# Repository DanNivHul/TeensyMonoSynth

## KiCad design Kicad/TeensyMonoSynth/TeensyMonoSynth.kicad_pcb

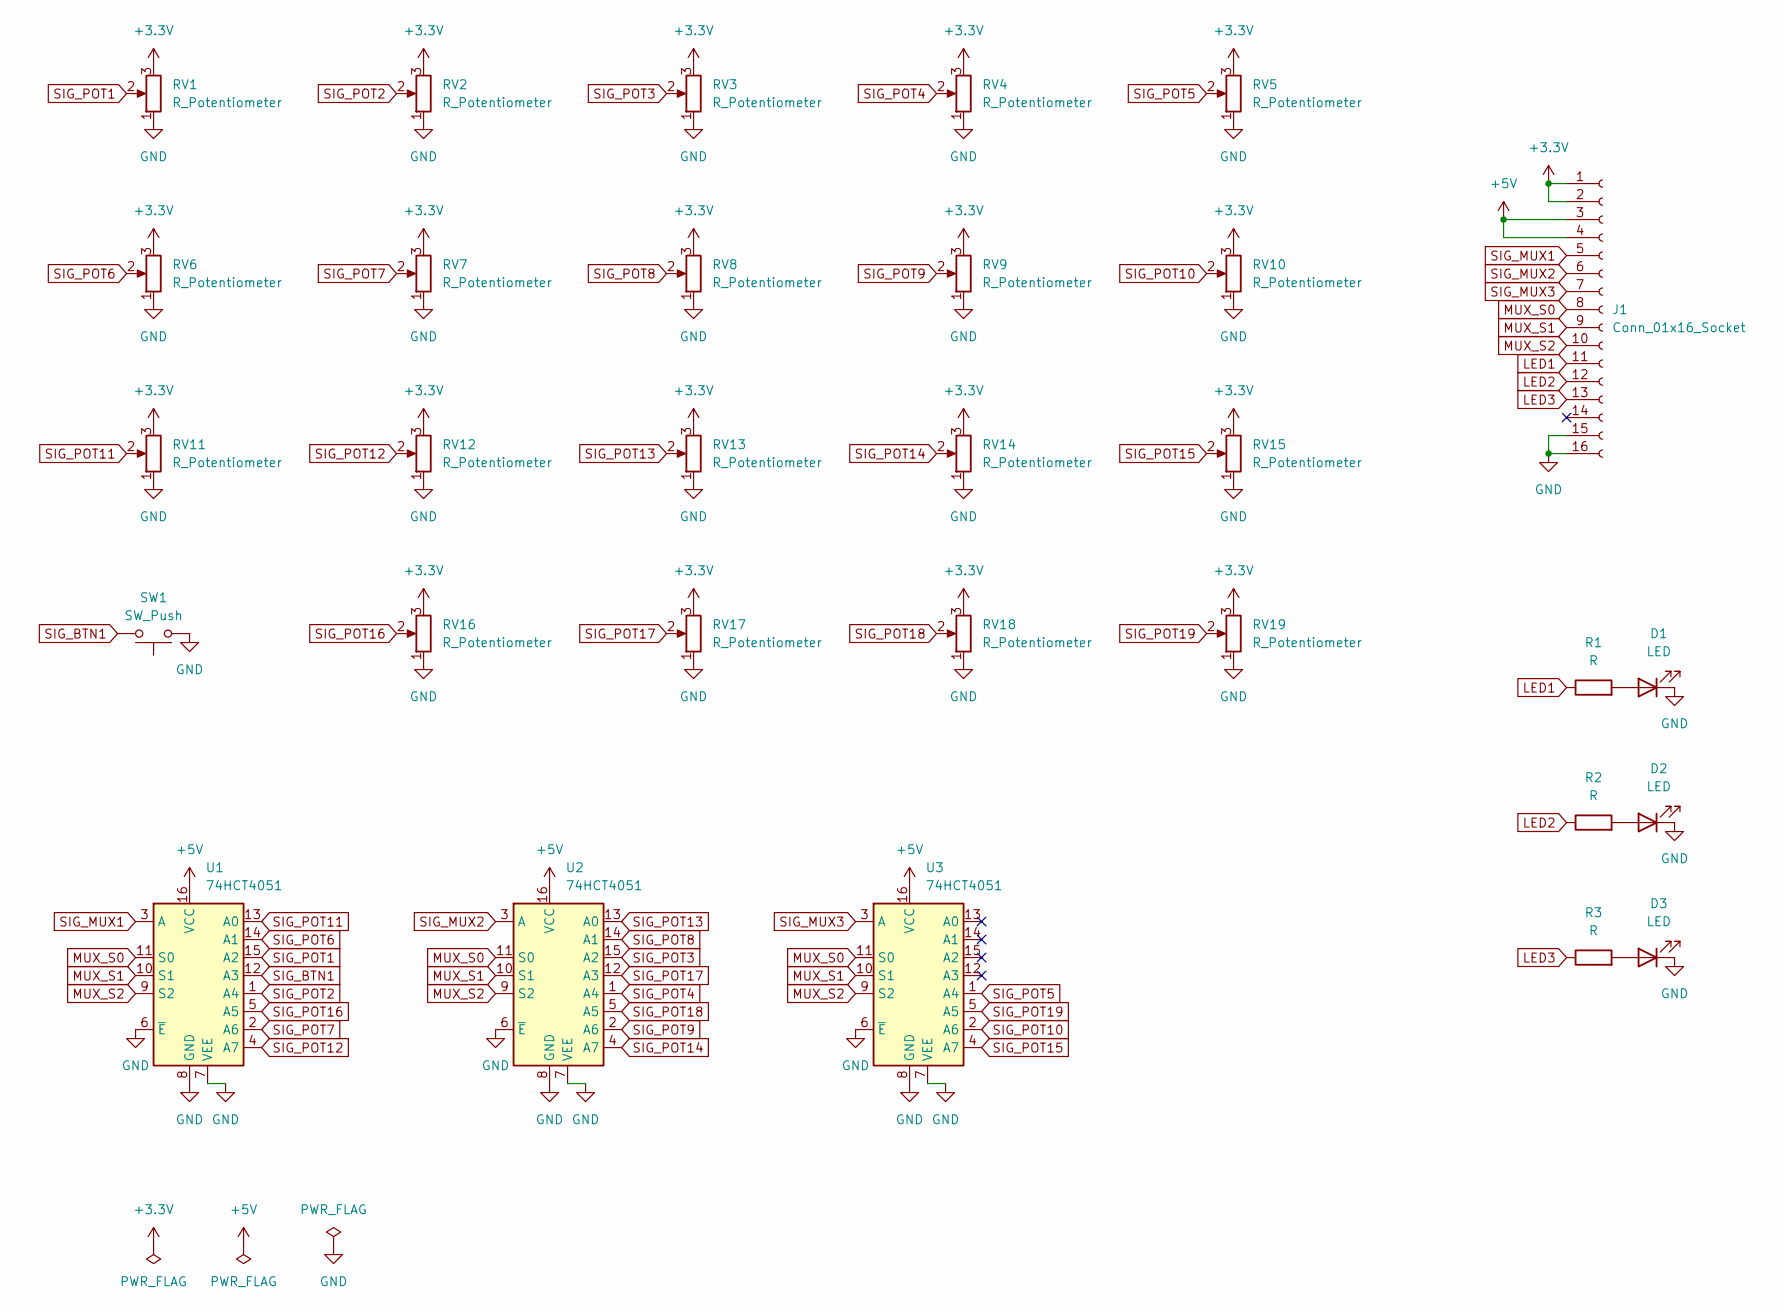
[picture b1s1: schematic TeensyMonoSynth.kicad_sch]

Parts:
D1, D2, D3: LED; LED_D3.0mm
J1: Conn_01x16_Socket; IDC-Header_2x08_P2.54mm_Vertical
R1, R2, R3: R; R_Axial_DIN0207_L6.3mm_D2.5mm_P10.16mm_Horizontal
RV1, RV2, RV3, RV4, RV5, RV6, RV7, RV8, RV9, RV10, RV11, RV12, RV13, RV14, RV15, RV16, RV17, RV18, RV19: R_Potentiometer; Potentiometer_Alps_RK09L_Single_Vertical
SW1: SW_Push; SW_PUSH-12mm
U1, U2, U3: 74HCT4051; DIP-16_W7.62mm

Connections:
+3.3V: J1.1, J1.2, RV1.3, RV2.3, RV3.3, RV4.3, RV5.3, RV6.3, RV7.3, RV8.3, RV9.3, RV10.3, RV11.3, RV12.3, RV13.3, RV14.3, RV15.3, RV16.3, RV17.3, RV18.3, RV19.3
+5V: J1.3, J1.4, U1.16 (VCC), U2.16 (VCC), U3.16 (VCC)
GND: D1.1 (K), D2.1 (K), D3.1 (K), J1.15, J1.16, RV1.1, RV2.1, RV3.1, RV4.1, RV5.1, RV6.1, RV7.1, RV8.1, RV9.1, RV10.1, RV11.1, RV12.1, RV13.1, RV14.1, RV15.1, RV16.1, RV17.1, RV18.1, RV19.1, SW1.1, U1.6 (~E), U1.7 (VEE), U1.8 (GND), U2.6 (~E), U2.7 (VEE), U2.8 (GND), U3.6 (~E), U3.7 (VEE), U3.8 (GND)
LED1: J1.11, R1.1
LED2: J1.12, R2.1
LED3: J1.13, R3.1
MUX_S0: J1.8, U1.11 (S0), U2.11 (S0), U3.11 (S0)
MUX_S1: J1.9, U1.10 (S1), U2.10 (S1), U3.10 (S1)
MUX_S2: J1.10, U1.9 (S2), U2.9 (S2), U3.9 (S2)
unnamed: D1.2 (A), R1.2
unnamed: D2.2 (A), R2.2
unnamed: D3.2 (A), R3.2
SIG_BTN1: SW1.2, U1.12 (A3)
SIG_MUX1: J1.5, U1.3 (A)
SIG_MUX2: J1.6, U2.3 (A)
SIG_MUX3: J1.7, U3.3 (A)
SIG_POT1: RV1.2, U1.15 (A2)
SIG_POT2: RV2.2, U1.1 (A4)
SIG_POT3: RV3.2, U2.15 (A2)
SIG_POT4: RV4.2, U2.1 (A4)
SIG_POT5: RV5.2, U3.1 (A4)
SIG_POT6: RV6.2, U1.14 (A1)
SIG_POT7: RV7.2, U1.2 (A6)
SIG_POT8: RV8.2, U2.14 (A1)
SIG_POT9: RV9.2, U2.2 (A6)
SIG_POT10: RV10.2, U3.2 (A6)
SIG_POT11: RV11.2, U1.13 (A0)
SIG_POT12: RV12.2, U1.4 (A7)
SIG_POT13: RV13.2, U2.13 (A0)
SIG_POT14: RV14.2, U2.4 (A7)
SIG_POT15: RV15.2, U3.4 (A7)
SIG_POT16: RV16.2, U1.5 (A5)
SIG_POT17: RV17.2, U2.12 (A3)
SIG_POT18: RV18.2, U2.5 (A5)
SIG_POT19: RV19.2, U3.5 (A5)

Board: 4 copper layers, 30 parts (3 on the bottom side), 35 nets, no tracks yet.

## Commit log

2024-12-23 add glide and store held notes
2024-12-23 add legato
2024-12-24 add band pass filter option
2024-12-24 rearranging files
2024-12-27 separate code into more files
2024-12-27 I think that is right
2024-12-28 pitch envelope
2024-12-29 change pulse to square
2024-12-29 better pitch envelope
2024-12-29 fixed glide time - turn on or off
2024-12-30 refactoring
2024-12-30 add velocity to amp modulation
2024-12-30 add osc cross modulation
2024-12-30 go back to previous technique for volume mod
2024-12-31 re-re-do note velocity to volume logic in gui
2024-12-31 rename cross mod to fm
2024-12-31 init values for velocity depth
    set initial values for velocity to volume modulation and velocity to filter modulation
2024-12-31 mod wheel sets lfo amplitude
2024-12-31 added pitch bend
2024-12-31 fuck yea seems to work
2025-01-06 init kicad project
2025-01-06 add teensy symbol and footprint libs
2025-01-18 PCB LAYOUT COMPLETE
